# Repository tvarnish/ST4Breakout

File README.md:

# ST-4 Autoguider Breakout board 
An open-source, versatile breakout board for controlling ST-4 autoguider ports on telescope mounts. Connect the board to the drive motors with an ST-4 cable (RJ12) and use a 5V microcontroller (e.g. Raspberry Pi GPIO or Arduino) to easily control the motor axes!

> :warning: **IMPORTANT:** I've only tested this with a **Skywatcher Enhanced Dual-Axis Motor Drive for EQ3-2 Mount**, so I can't guarantee it'll work with every autoguider-compatible telescope mount! If you've tried this on another 'scope, let me know if it was successful!

To trigger an axis, pull the corresponding input header pin HIGH (5V). This breakout board can be used for dual-axis control at a single slewing speed (set by the motor drive handset).

> :warning: **ANOTHER IMPORTANT NOTE:** Only trigger a single axis (HIGH) at a time. There isn't anything (yet) in the hardware that will prevent this, so make sure it doesn't ever happen through software.

I had the v0.1 board printed with [JLCPCB](https://jlcpcb.com/), as seen in the image above.

All of the KiCAD files (and gerbers) for the breakout can be found in the `/ST4Breakout` directory.

## Required Components
To construct the board, along with the PCB you'll also need the following components:

Component | Quantity
----------|---------
[RJ12 Socket](https://uk.rs-online.com/web/p/products/2400929/) | 1
[100 Ohm Resistor](https://uk.rs-online.com/web/p/products/7078625/) | 4
[TIL196 Phototransistor Optocoupler](https://uk.rs-online.com/web/p/products/1611233/) | 1
[16-pin IC DIP Socket](https://uk.rs-online.com/web/p/products/0402771/) | 1
[Single-row 2.54 mm Header Pins](https://uk.rs-online.com/web/p/products/2518632/) | 5 pins

*(All links provided are for RS Components UK)*
Component footprints and 3D models are provided for these specified components. Equivalent parts may work, but their footprints may be slightly different, so I can't guarantee they'll fit the PCB.

## Additional Board Images

Front and back of the board (unpopulated). Ballpoint pen lid for scale. I thought a banana would be a bit too big. And... I didn't have one to hand.

Gerber renders for the front and back of the PCB.

## Circuit Description
I've provided a basic explanation for the operation of the breakout board below, in case it helps you to decide if the board will work for your mount (if it isn't a Skywatcher EQ3-2). **Note: I can't guarantee if this will work for your mount/drive! Use at your own risk!**

Each "axis" (e.g. RA/DEC) has a positive and negative trigger pin (to drive the motor forwards or backwards). Applying a 5V signal to one of these pins will "trigger" the telescope axis to move in that specific direction.

Each trigger pin is connected (via a current limiting resistor) to one input of a quad-input optocoupler IC (TIL196). This connects the microcontroller circuit to the telescope motor drive circuit, isolating each side. Triggering an axis will connect the corresponding wire in the ST-4 cable to ground, completing the controller-side circuit. The optocoupler IC is necessary to ensure that the higher voltage/current on the motor controller side doesn't break the microcontroller!

## Author
Created by Thomas Varnish. Find me [@tvarnish](https://github.com/tvarnish) on GitHub and [@ThomasVarnish](https://twitter.com/ThomasVarnish) on Twitter :smiley:

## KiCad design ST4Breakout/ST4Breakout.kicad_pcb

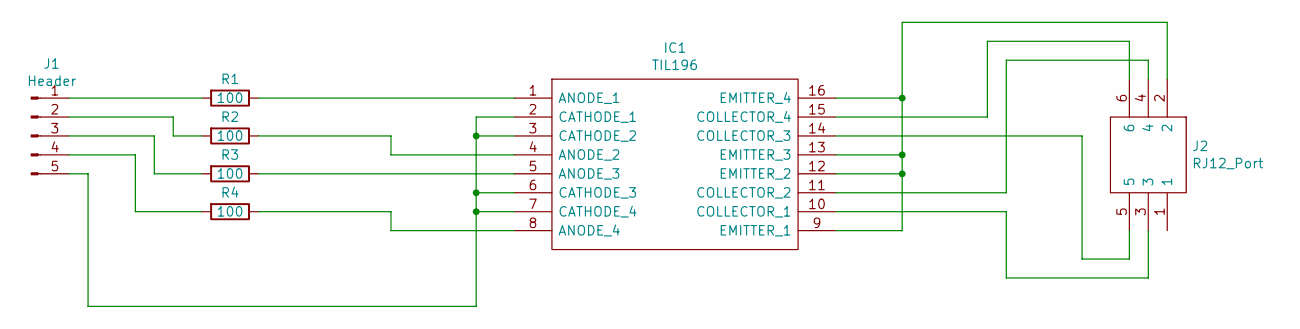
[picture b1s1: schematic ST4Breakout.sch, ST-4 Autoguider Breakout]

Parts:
IC1: TIL196; TIL196_Optocoupler_THT; Manufacturer_Part_Number TIL196
J1: Header; PinHeader_1x05_P2.54mm_Vertical
J2: RJ12_Port; RJ12_Female_THT_Connector; Manufacturer_Part_Number 95501-2661; Mouser Part Number 538-95501-2661
R1, R2, R3, R4: 100; R_Axial_DIN0309_L9.0mm_D3.2mm_P12.70mm_Horizontal

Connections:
unnamed: IC1.1 (ANODE_1), R1.1
unnamed: IC1.2 (CATHODE_1), IC1.3 (CATHODE_2), IC1.6 (CATHODE_3), IC1.7 (CATHODE_4), J1.5
unnamed: IC1.4 (ANODE_2), R2.1
unnamed: IC1.5 (ANODE_3), R3.1
unnamed: IC1.8 (ANODE_4), R4.1
unnamed: IC1.10 (COLLECTOR_1), J2.3
unnamed: IC1.11 (COLLECTOR_2), J2.4
unnamed: IC1.9 (EMITTER_1), IC1.12 (EMITTER_2), IC1.13 (EMITTER_3), IC1.16 (EMITTER_4), J2.2
unnamed: IC1.14 (COLLECTOR_3), J2.5
unnamed: IC1.15 (COLLECTOR_4), J2.6
unnamed: J1.1, R1.2
unnamed: J1.2, R2.2
unnamed: J1.3, R3.2
unnamed: J1.4, R4.2

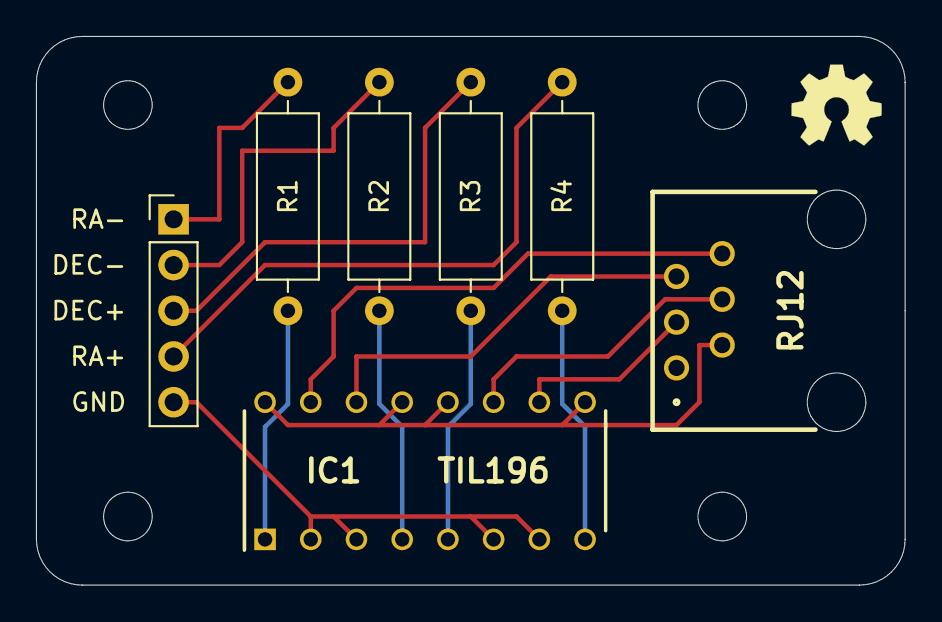
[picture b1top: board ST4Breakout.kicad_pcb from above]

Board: 2 copper layers, 48.3 x 30.5 mm, 7 parts (0 on the bottom side), 14 nets.

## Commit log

2020-06-13 Update .gitignore and remove ignored files
    Update .gitignore to ignore .sch-bak files, and remove these files from
    the repository (since they were incorrectly added at the initial
    commit).
2020-07-02 Update README.md
    Add details for the project, images, and basic instructions for use.
2020-07-02 Add schematic to README.md
2020-07-02 Update README.md
    Fix the wording of the circuit description.
